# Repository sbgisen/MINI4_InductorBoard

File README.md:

# MINI4_InductorBoard
Schematic of additional inductor board for mini4 based servo driver

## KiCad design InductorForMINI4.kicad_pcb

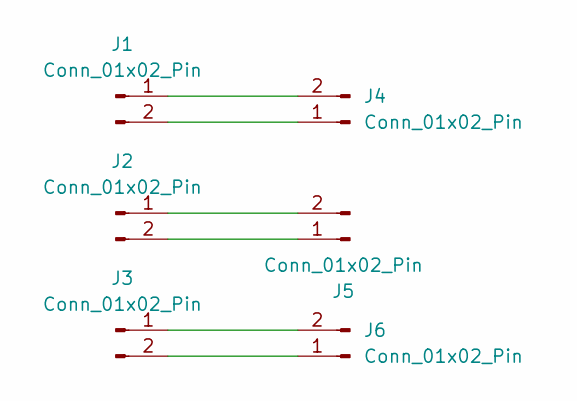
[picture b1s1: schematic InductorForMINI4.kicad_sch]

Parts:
J1, J2, J3: Conn_01x02_Pin; Inductor_pad
J4, J5, J6: Conn_01x02_Pin; InductorMINI4

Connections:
unnamed: J1.1, J4.2
unnamed: J1.2, J4.1
unnamed: J2.1, J5.2
unnamed: J2.2, J5.1
unnamed: J3.1, J6.2
unnamed: J3.2, J6.1

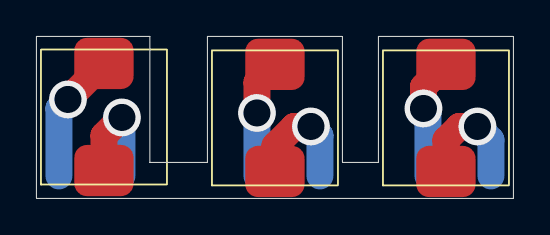
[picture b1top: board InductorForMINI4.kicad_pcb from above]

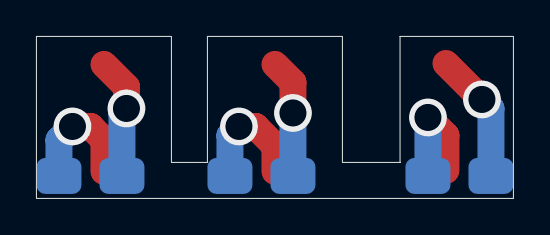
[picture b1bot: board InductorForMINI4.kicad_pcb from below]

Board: 2 copper layers, 26.5 x 9.0 mm, 6 parts (3 on the bottom side), 6 nets.

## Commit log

2026-02-06 feat: add schematic of inductor board for mini servo driver
2026-02-06 fix: avoid touching inductor with bldc motor
